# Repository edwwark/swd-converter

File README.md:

# swd-converter
 STDC14 / MIPI10 / ARM10 / 4x2pin conversion board

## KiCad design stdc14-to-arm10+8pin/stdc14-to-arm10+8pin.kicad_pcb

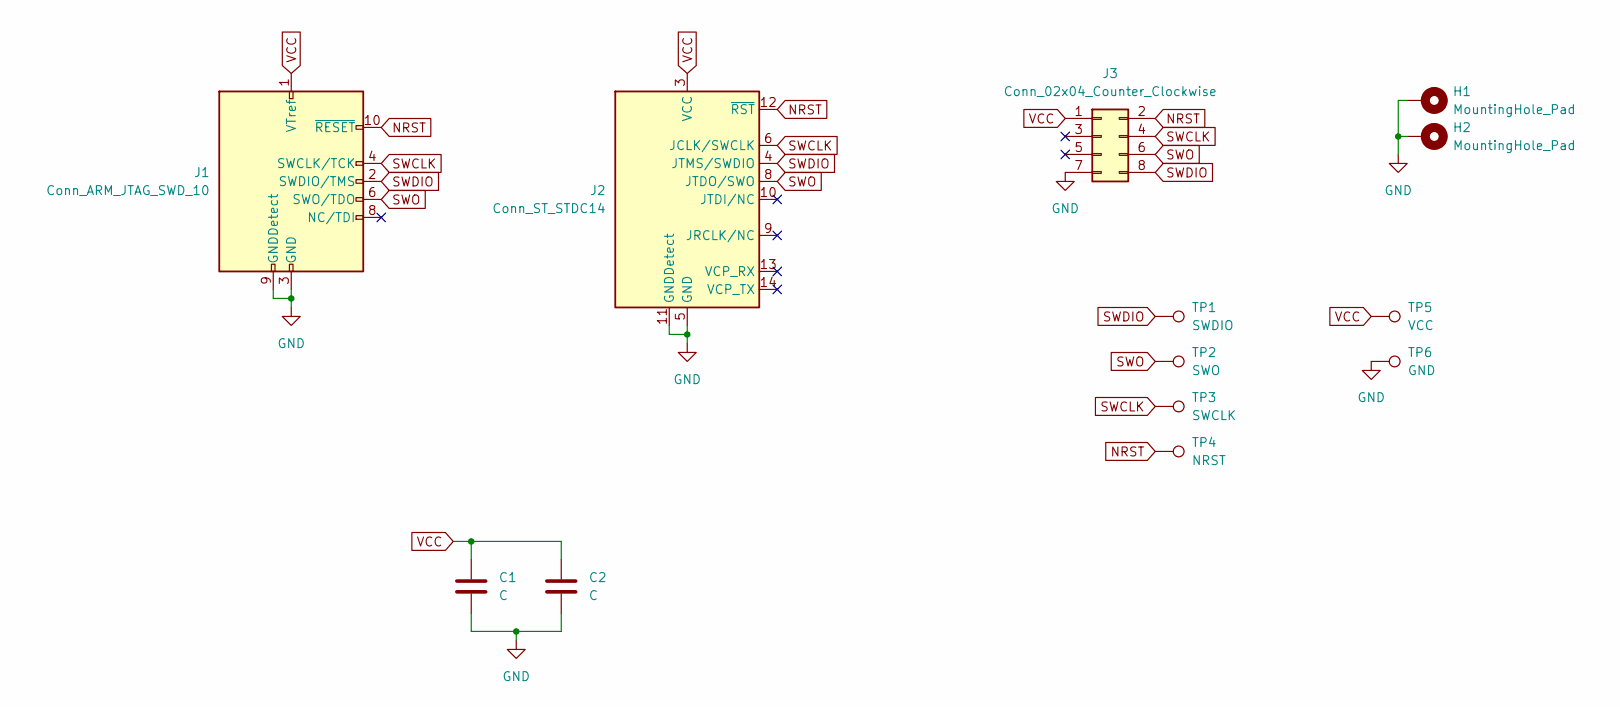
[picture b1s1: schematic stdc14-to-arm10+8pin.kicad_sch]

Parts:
C1, C2: C; C_0805_2012Metric
H1, H2: MountingHole_Pad; MountingHole_2.7mm_M2.5_Pad
J1: Conn_ARM_JTAG_SWD_10; IDC-Header_2x05_P2.54mm_Vertical
J2: Conn_ST_STDC14; PinSocket_2x07_P1.27mm_Vertical_SMD
J3: Conn_02x04_Counter_Clockwise; IDC-Header_2x04_P2.54mm_Vertical
TP1: SWDIO; TestPoint_Pad_D1.0mm
TP2: SWO; TestPoint_Pad_D1.0mm
TP3: SWCLK; TestPoint_Pad_D1.0mm
TP4: NRST; TestPoint_Pad_D1.0mm
TP5: VCC; TestPoint_Pad_D1.0mm
TP6: GND; TestPoint_Pad_D1.0mm

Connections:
GND: C1.2, C2.2, H1.1, H2.1, J1.3 (GND), J1.5 (GND), J1.9 (GNDDetect), J2.5 (GND), J2.7 (GND), J2.11 (GNDDetect), J3.7, TP6.1
NRST: J1.10 (~RESET), J2.12 (~RST), J3.2, TP4.1
SWCLK: J1.4 (SWCLK/TCK), J2.6 (JCLK/SWCLK), J3.4, TP3.1
SWDIO: J1.2 (SWDIO/TMS), J2.4 (JTMS/SWDIO), J3.8, TP1.1
SWO: J1.6 (SWO/TDO), J2.8 (JTDO/SWO), J3.6, TP2.1
VCC: C1.1, C2.1, J1.1 (VTref), J2.3 (VCC), J3.1, TP5.1

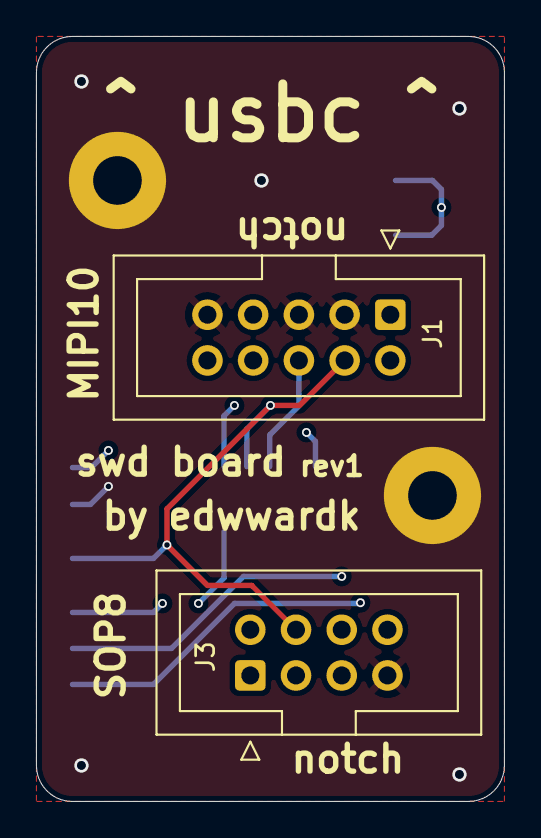
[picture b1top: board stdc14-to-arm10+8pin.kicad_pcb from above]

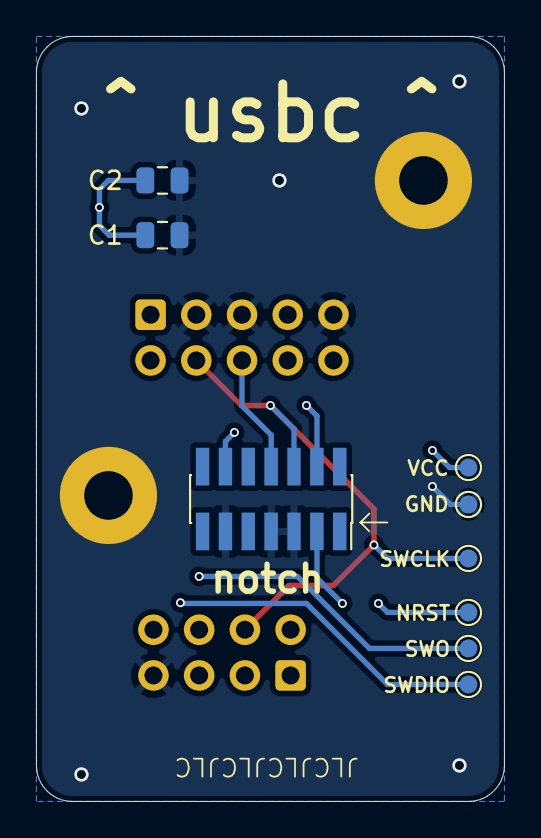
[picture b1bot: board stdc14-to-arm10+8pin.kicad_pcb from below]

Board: 6 copper layers, 26.0 x 42.5 mm, 13 parts (9 on the bottom side), 6 nets.

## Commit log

2024-04-04 init, added symbols+footprints, need check
2024-04-04 put soicbite onto pcb
2024-04-04 slight shifts
2024-04-05 prob fin?
2024-04-05 unlock
2024-04-05 moved some traces, add decoupling
2024-04-06 moved couple things
2024-04-06 probably ready for manufacture
2024-04-07 rev1
